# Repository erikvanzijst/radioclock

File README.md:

# Radio Controlled Clock

This project contains a custom designed wall clock that syncs to the DCF77
atomic time broadcast radio signal from Germany to ensure accuracy at all
times. There are no buttons to set the time manually.

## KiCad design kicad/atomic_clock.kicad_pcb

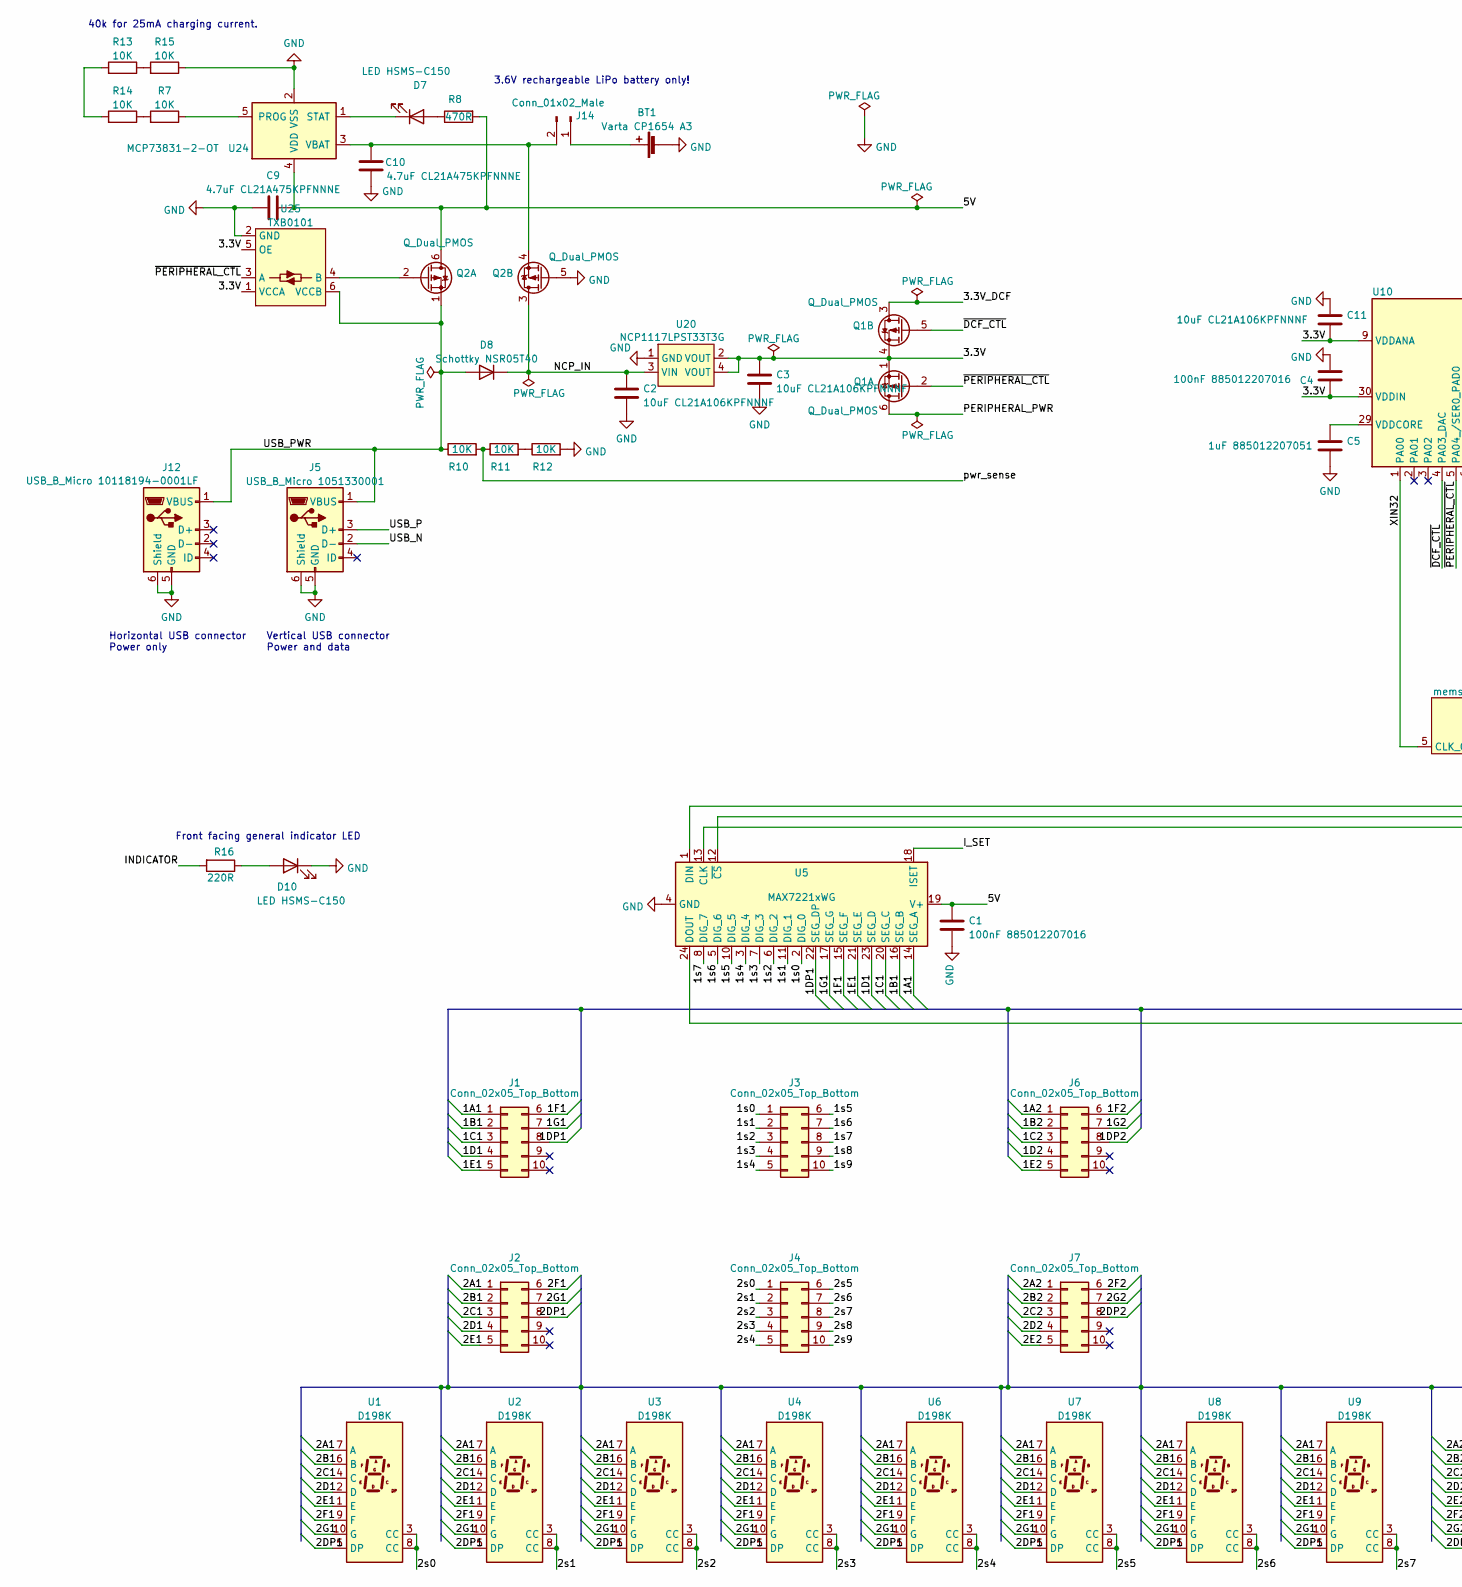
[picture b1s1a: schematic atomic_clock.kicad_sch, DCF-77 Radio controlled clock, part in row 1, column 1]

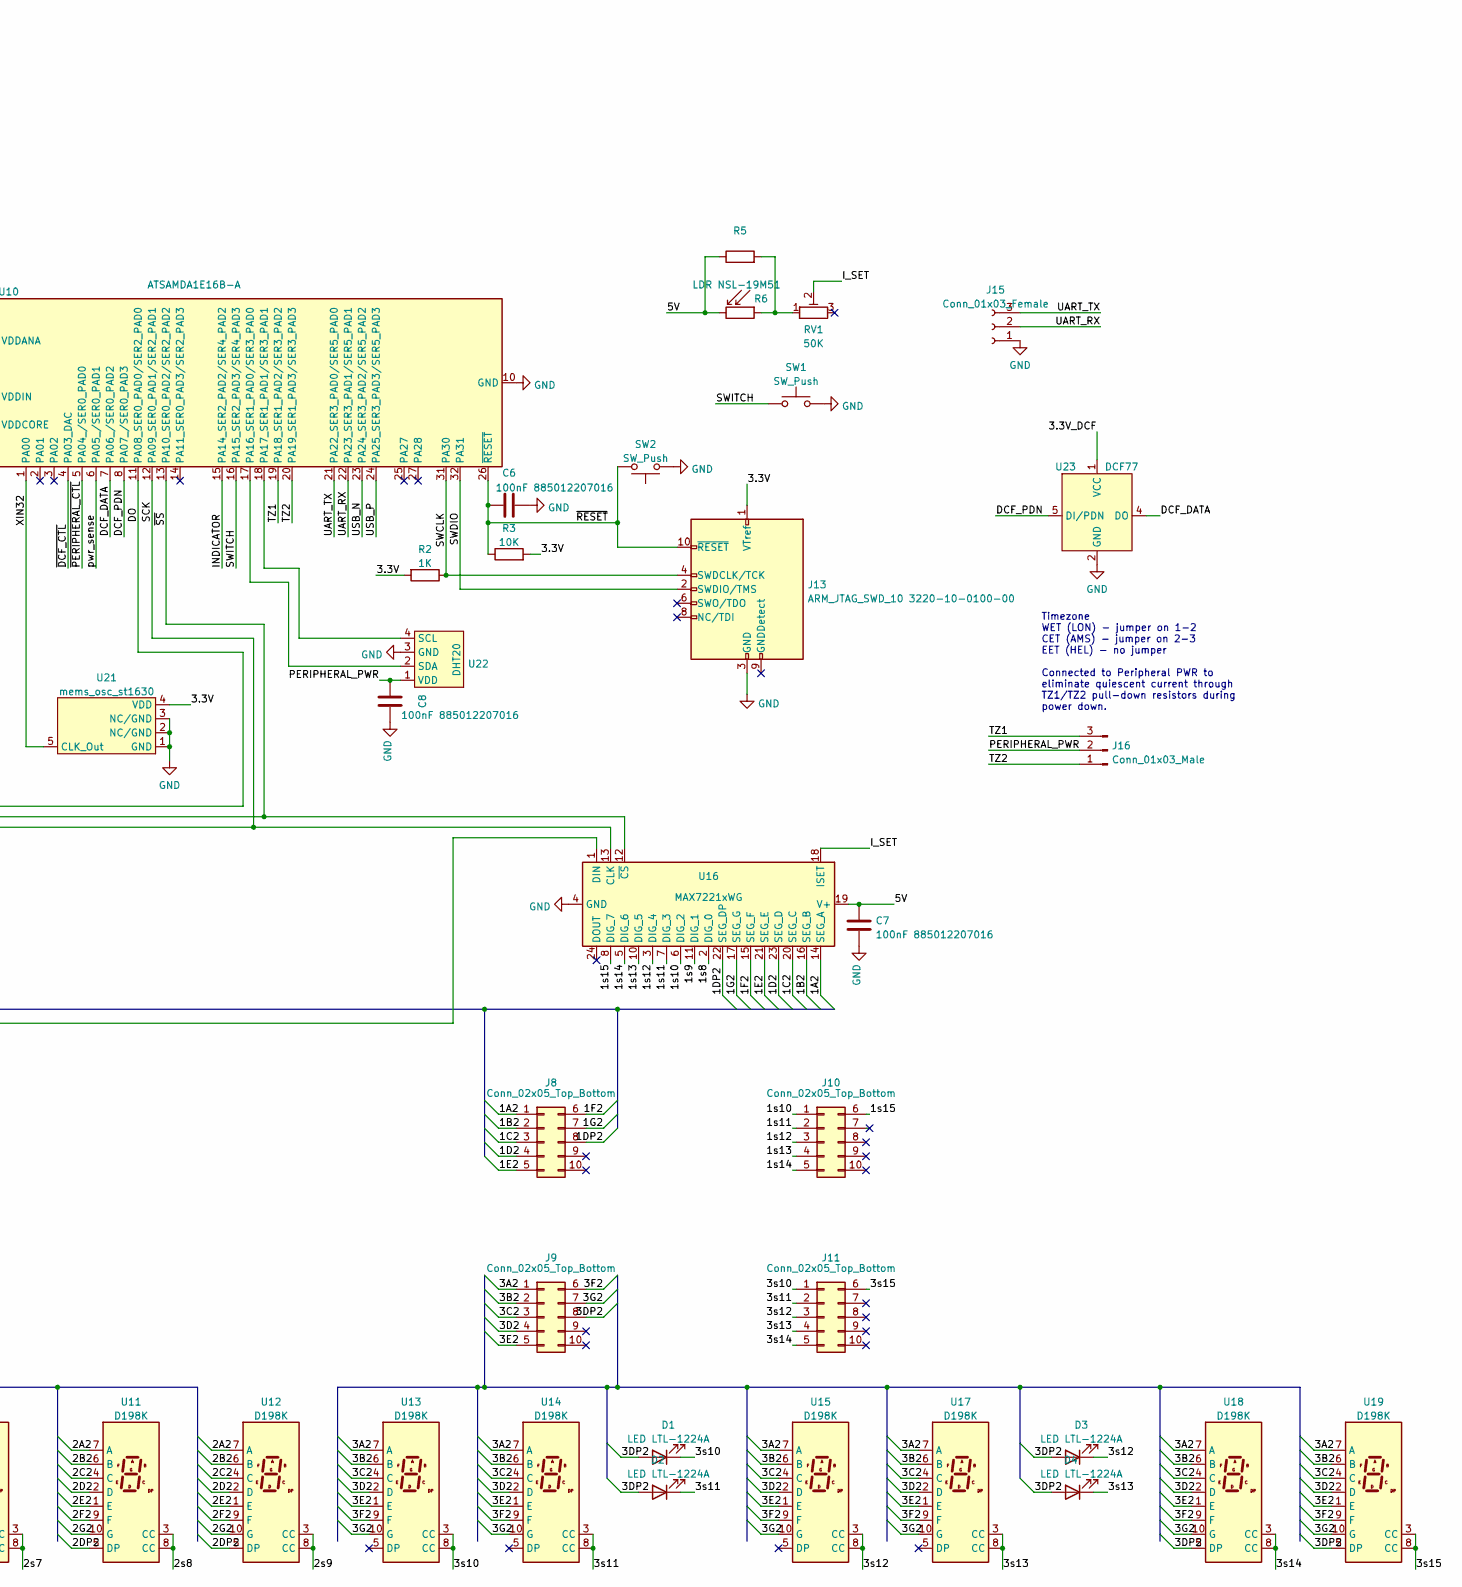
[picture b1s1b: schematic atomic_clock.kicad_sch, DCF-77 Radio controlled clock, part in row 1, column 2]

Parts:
BT1: Varta CP1654 A3; Battery_pads
C1, C4, C6, C7, C8: 100nF 885012207016; C_0805_2012Metric
C2, C3, C11: 10uF CL21A106KPFNNNF; C_0805_2012Metric
C5: 1uF 885012207051; C_0805_2012Metric
C9, C10: 4.7uF CL21A475KPFNNNE; C_0805_2012Metric
D1, D2, D3, D4: LED LTL-1224A; LED_D2.0mm_W4.8mm_H2.5mm_FlatTop
D7, D10: LED HSMS-C150; LED_1206_3216Metric_Pad1.42x1.75mm_HandSolder
D8: Schottky NSR05T40; D_SOD-523
J1, J2, J3, J4, J6, J7, J8, J9, J10, J11: Conn_02x05_Top_Bottom; PinHeader_2x05_P2.54mm_Vertical; DigiKey 67996-400HLF
J5: USB_B_Micro 1051330001; USB_Micro-B_Molex-105133-0001
J12: USB_B_Micro 10118194-0001LF; USB_Micro-B_Amphenol_10118194_Horizontal
J13: ARM_JTAG_SWD_10 3220-10-0100-00; sam_swd_header
J14: Conn_01x02_Male; PinHeader_1x02_P2.54mm_Vertical
J15: Conn_01x03_Female; PinSocket_1x03_P2.54mm_Vertical
J16: Conn_01x03_Male; PinHeader_1x03_P2.54mm_Vertical
Q1, Q2: Q_Dual_PMOS; SOT-363_SC-70-6
R2: 1K; R_0805_2012Metric
R3, R7, R10, R11, R12, R13, R14, R15: 10K; R_0805_2012Metric
R5: R_0805_2012Metric
R6: LDR NSL-19M51; R_LDR_4.9x4.2mm_P2.54mm_Vertical
R8: 470R; R_0805_2012Metric
R16: 220R; R_0805_2012Metric
RV1: 50K; Potentiometer_Bourns_TC33X_Vertical
SW1, SW2: SW_Push; SW_SPST_TL3342
U1, U2, U3, U4, U6, U7, U8, U9, U11, U12, U13, U14, U15, U17, U18, U19: D198K; D1X8K
U5, U16: MAX7221xWG; SOIC-24W_7.5x15.4mm_P1.27mm
U10: ATSAMDA1E16B-A; TQFP-32_7x7mm_P0.8mm
U20: NCP1117LPST33T3G; SOT-223
U21: mems_osc_st1630; SOT-23-5
U22: DHT20
U23: DCF77; DCF77 receiver module
U24: MCP73831-2-OT; SOT-23-5
U25: TXB0101; SOT-363_SC-70-6

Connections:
/1A1: J1.1, U5.14 (SEG_A)
/1A2: J6.1, J8.1, U16.14 (SEG_A)
/1B1: J1.2, U5.16 (SEG_B)
/1B2: J6.2, J8.2, U16.16 (SEG_B)
/1C1: J1.3, U5.20 (SEG_C)
/1C2: J6.3, J8.3, U16.20 (SEG_C)
/1D1: J1.4, U5.23 (SEG_D)
/1D2: J6.4, J8.4, U16.23 (SEG_D)
/1DP1: J1.8, U5.22 (SEG_DP)
/1DP2: J6.8, J8.8, U16.22 (SEG_DP)
/1E1: J1.5, U5.21 (SEG_E)
/1E2: J6.5, J8.5, U16.21 (SEG_E)
/1F1: J1.6, U5.15 (SEG_F)
/1F2: J6.6, J8.6, U16.15 (SEG_F)
/1G1: J1.7, U5.17 (SEG_G)
/1G2: J6.7, J8.7, U16.17 (SEG_G)
/1s0: J3.1, U5.2 (DIG_0)
/1s1: J3.2, U5.11 (DIG_1)
/1s2: J3.3, U5.6 (DIG_2)
/1s3: J3.4, U5.7 (DIG_3)
/1s4: J3.5, U5.3 (DIG_4)
/1s5: J3.6, U5.10 (DIG_5)
/1s6: J3.7, U5.5 (DIG_6)
/1s7: J3.8, U5.8 (DIG_7)
/1s8: J3.9, U16.2 (DIG_0)
/1s9: J3.10, U16.11 (DIG_1)
/1s10: J10.1, U16.6 (DIG_2)
/1s11: J10.2, U16.7 (DIG_3)
/1s12: J10.3, U16.3 (DIG_4)
/1s13: J10.4, U16.10 (DIG_5)
/1s14: J10.5, U16.5 (DIG_6)
/1s15: J10.6, U16.8 (DIG_7)
/2A1: J2.1, U1.7 (A), U2.7 (A), U3.7 (A), U4.7 (A), U6.7 (A), U7.7 (A), U8.7 (A), U9.7 (A)
/2A2: J7.1, U11.7 (A), U12.7 (A)
/2B1: J2.2, U1.6 (B), U2.6 (B), U3.6 (B), U4.6 (B), U6.6 (B), U7.6 (B), U8.6 (B), U9.6 (B)
/2B2: J7.2, U11.6 (B), U12.6 (B)
/2C1: J2.3, U1.4 (C), U2.4 (C), U3.4 (C), U4.4 (C), U6.4 (C), U7.4 (C), U8.4 (C), U9.4 (C)
/2C2: J7.3, U11.4 (C), U12.4 (C)
/2D1: J2.4, U1.2 (D), U2.2 (D), U3.2 (D), U4.2 (D), U6.2 (D), U7.2 (D), U8.2 (D), U9.2 (D)
/2D2: J7.4, U11.2 (D), U12.2 (D)
/2DP1: J2.8, U1.5 (DP), U2.5 (DP), U3.5 (DP), U4.5 (DP), U6.5 (DP), U7.5 (DP), U8.5 (DP), U9.5 (DP)
/2DP2: J7.8, U11.5 (DP), U12.5 (DP)
/2E1: J2.5, U1.1 (E), U2.1 (E), U3.1 (E), U4.1 (E), U6.1 (E), U7.1 (E), U8.1 (E), U9.1 (E)
/2E2: J7.5, U11.1 (E), U12.1 (E)
/2F1: J2.6, U1.9 (F), U2.9 (F), U3.9 (F), U4.9 (F), U6.9 (F), U7.9 (F), U8.9 (F), U9.9 (F)
/2F2: J7.6, U11.9 (F), U12.9 (F)
/2G1: J2.7, U1.10 (G), U2.10 (G), U3.10 (G), U4.10 (G), U6.10 (G), U7.10 (G), U8.10 (G), U9.10 (G)
/2G2: J7.7, U11.10 (G), U12.10 (G)
/2s0: J4.1, U1.3 (CC), U1.8 (CC)
/2s1: J4.2, U2.3 (CC), U2.8 (CC)
/2s2: J4.3, U3.3 (CC), U3.8 (CC)
/2s3: J4.4, U4.3 (CC), U4.8 (CC)
/2s4: J4.5, U6.3 (CC), U6.8 (CC)
/2s5: J4.6, U7.3 (CC), U7.8 (CC)
/2s6: J4.7, U8.3 (CC), U8.8 (CC)
/2s7: J4.8, U9.3 (CC), U9.8 (CC)
/2s8: J4.9, U11.3 (CC), U11.8 (CC)
/2s9: J4.10, U12.3 (CC), U12.8 (CC)
/3.3V: C3.1, C4.1, C11.1, J13.1 (VTref), Q1.1 (S), Q1.4 (S), R2.2, R3.2, U10.9 (VDDANA), U10.30 (VDDIN), U20.2 (VOUT), U20.4 (VOUT), U21.4 (VDD), U25.1 (VCCA), U25.5 (OE)
/3.3V_DCF: Q1.3 (D), U23.1 (VCC)
/3A2: J9.1, U13.7 (A), U14.7 (A), U15.7 (A), U17.7 (A), U18.7 (A), U19.7 (A)
/3B2: J9.2, U13.6 (B), U14.6 (B), U15.6 (B), U17.6 (B), U18.6 (B), U19.6 (B)
/3C2: J9.3, U13.4 (C), U14.4 (C), U15.4 (C), U17.4 (C), U18.4 (C), U19.4 (C)
/3D2: J9.4, U13.2 (D), U14.2 (D), U15.2 (D), U17.2 (D), U18.2 (D), U19.2 (D)
/3DP2: D1.2 (A), D2.2 (A), D3.2 (A), D4.2 (A), J9.8, U18.5 (DP), U19.5 (DP)
/3E2: J9.5, U13.1 (E), U14.1 (E), U15.1 (E), U17.1 (E), U18.1 (E), U19.1 (E)
/3F2: J9.6, U13.9 (F), U14.9 (F), U15.9 (F), U17.9 (F), U18.9 (F), U19.9 (F)
/3G2: J9.7, U13.10 (G), U14.10 (G), U15.10 (G), U17.10 (G), U18.10 (G), U19.10 (G)
/3s10: D1.1 (K), J11.1, U13.3 (CC), U13.8 (CC)
/3s11: D2.1 (K), J11.2, U14.3 (CC), U14.8 (CC)
/3s12: D3.1 (K), J11.3, U15.3 (CC), U15.8 (CC)
/3s13: D4.1 (K), J11.4, U17.3 (CC), U17.8 (CC)
/3s14: J11.5, U18.3 (CC), U18.8 (CC)
/3s15: J11.6, U19.3 (CC), U19.8 (CC)
/5V: C1.1, C7.1, C9.1, Q2.6 (D), R5.1, R6.2, R8.2, U5.19 (V+), U16.19 (V+), U24.4 (VDD)
/DCF_DATA: U10.7 (PA06_/SER0_PAD2), U23.4 (DO)
/DCF_PDN: U10.8 (PA07_/SER0_PAD3), U23.5 (DI/PDN)
/DO: U5.1 (DIN), U10.11 (PA08_SER0_PAD0/SER2_PAD0)
/INDICATOR: R16.2, U10.15 (PA14_SER2_PAD2/SER4_PAD2)
/I_SET: RV1.2, U5.18 (ISET), U16.18 (ISET)
/NCP_IN: C2.1, D8.1 (K), Q2.3 (D), U20.3 (VIN)
/PERIPHERAL_PWR: C8.1, J16.2, Q1.6 (D), U22.1 (VDD)
/SCK: U5.13 (CLK), U10.12 (PA09_SER0_PAD1/SER2_PAD1), U16.13 (CLK)
/SWCLK: J13.4 (SWDCLK/TCK), R2.1, U10.31 (PA30)
/SWDIO: J13.2 (SWDIO/TMS), U10.32 (PA31)
/SWITCH: SW1.1, U10.16 (PA15_SER2_PAD3/SER4_PAD3)
/TZ1: J16.3, U10.19 (PA18_SER1_PAD2/SER3_PAD2)
/TZ2: J16.1, U10.20 (PA19_SER1_PAD3/SER3_PAD3)
/UART_RX: J15.2, U10.22 (PA23_SER3_PAD1/SER5_PAD1)
/UART_TX: J15.3, U10.21 (PA22_SER3_PAD0/SER5_PAD0)
/USB_N: J5.2 (D-), U10.23 (PA24_SER3_PAD2/SER5_PAD2)
/USB_P: J5.3 (D+), U10.24 (PA25_SER3_PAD3/SER5_PAD3)
/USB_PWR: D8.2 (A), J5.1 (VBUS), J12.1 (VBUS), Q2.1 (S), R10.1, U25.6 (VCCB)
/XIN32: U10.1 (PA00), U21.5 (CLK_Out)
/pwr_sense: R10.2, R11.1, U10.6 (PA05_/SER0_PAD1)
/~DCF_CTL: Q1.5 (G), U10.4 (PA03_DAC)
/~PERIPHERAL_CTL: Q1.2 (G), U10.5 (PA04_/SER0_PAD0), U25.3 (A)
/~RESET: C6.1, J13.10 (~RESET), R3.1, SW2.2, U10.26 (~RESET)
/~SS: U5.12 (~CS), U10.13 (PA10_SER0_PAD2/SER2_PAD2), U16.12 (~CS)
GND: BT1.2 (-), C1.2, C2.2, C3.2, C4.2, C5.2, C6.2, C7.2, C8.2, C9.2, C10.1, C11.2, D10.1 (K), J5.5 (GND), J5.6 (Shield), J12.5 (GND), J12.6 (Shield), J13.3 (GND), J13.5 (GND), J15.1, Q2.5 (G), R12.2, R15.1, SW1.2, SW2.1, U5.4 (GND), U5.9 (GND), U10.10 (GND), U10.28 (GND), U16.4 (GND), U16.9 (GND), U20.1 (GND), U21.1 (GND), U21.2 (NC/GND), U21.3 (NC/GND), U22.3 (GND), U23.2 (GND), U24.2 (VSS), U25.2 (GND)
unnamed: BT1.1 (+), J14.1
unnamed: C5.1, U10.29 (VDDCORE)
unnamed: C10.2, J14.2, Q2.4 (S), U24.3 (VBAT)
unnamed: D7.1 (K), U24.1 (STAT)
unnamed: D7.2 (A), R8.1
unnamed: D10.2 (A), R16.1
unnamed: Q2.2 (G), U25.4 (B)
unnamed: R5.2, R6.1, RV1.1
unnamed: R7.1, U24.5 (PROG)
unnamed: R11.2, R12.1
unnamed: R13.1, R15.2
unnamed: R13.2, R14.2
unnamed: R7.2, R14.1
unnamed: U10.17 (PA16_SER1_PAD0/SER3_PAD0), U22.2 (SDA)
unnamed: U10.18 (PA17_SER1_PAD1/SER3_PAD1), U22.4 (SCL)
unnamed: U5.24 (DOUT), U16.1 (DIN)

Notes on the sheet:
40k for 25mA charging current.
Front facing general indicator LED
Vertical USB connector Power and data
3.6V rechargeable LiPo battery only!
Timezone WET (LON) - jumper on 1-2 CET (AMS) - jumper on 2-3 EET (HEL) - no jumper Connected to Peripheral PWR to eliminate quiescent current through TZ1/TZ2 pull-down resistors during power down.
Horizontal USB connector Power only

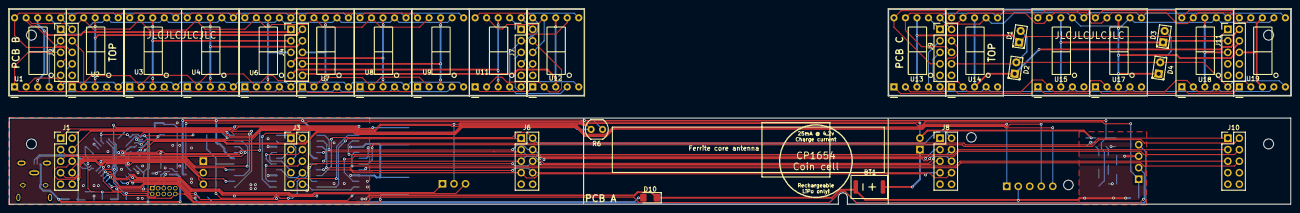
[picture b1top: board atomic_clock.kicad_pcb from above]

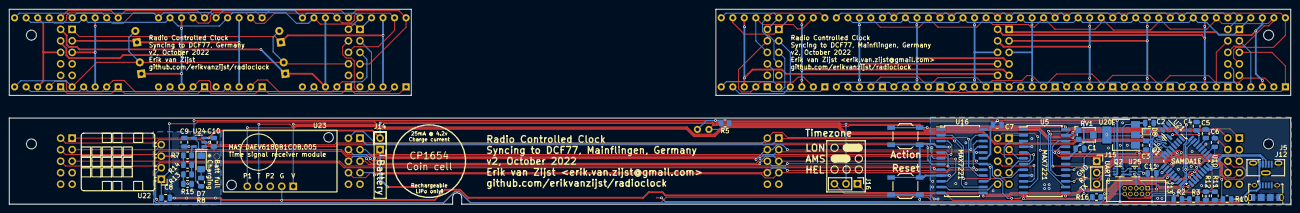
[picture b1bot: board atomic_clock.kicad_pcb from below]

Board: 2 copper layers, 282.7 x 43.0 mm, 78 parts (45 on the bottom side), 116 nets.

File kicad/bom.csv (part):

"Source:","/Users/erik/work/atomic_clock/kicad/atomic_clock.kicad_sch"
"Date:","Monday, June 06, 2022 at 12:07:27 AM"
"Tool:","Eeschema (6.0.4-0)"
"Generator:","/Applications/KiCad/KiCad.app/Contents/SharedSupport/plugins/bom_csv_grouped_by_value.py"
"Component Count:","80"

"Individual Components:"

"Item","Qty","Reference(s)","Value","LibPart","Footprint","Datasheet","Mfr","Mfr No.","Notes"
"","","BT1","Varta CP1654 A3","Device:Battery_Cell","local_footprints:Battery_pads","https://www.texim-europe.com/product/63165201018-VAR","","",""
"","","C1","100nF 885012207016","Device:C","Capacitor_SMD:C_0805_2012Metric","https://www.mouser.be/datasheet/2/445/885012207016-1727611.pdf","","",""
"","","C2","10uF CL21A106KPFNNNF","Device:C","Capacitor_SMD:C_0805_2012Metric","https://www.mouser.be/datasheet/2/585/MLCC-1837944.pdf","","",""
"","","C3","10uF CL21A106KPFNNNF","Device:C","Capacitor_SMD:C_0805_2012Metric","https://www.mouser.be/datasheet/2/585/MLCC-1837944.pdf","","",""
"","","C4","100nF 885012207016","Device:C","Capacitor_SMD:C_0805_2012Metric","https://www.mouser.be/datasheet/2/445/885012207016-1727611.pdf","","",""
"","","C5","1uF 885012207051","Device:C","Capacitor_SMD:C_0805_2012Metric","https://www.mouser.be/datasheet/2/445/885012207051-1727669.pdf","","",""
"","","C6","100nF 885012207016","Device:C","Capacitor_SMD:C_0805_2012Metric","https://www.mouser.be/datasheet/2/445/885012207016-1727611.pdf","","",""
"","","C7","100nF 885012207016","Device:C","Capacitor_SMD:C_0805_2012Metric","https://www.mouser.be/datasheet/2/445/885012207016-1727611.pdf","","",""
"","","C8","100nF 885012207016","Device:C","Capacitor_SMD:C_0805_2012Metric","https://www.mouser.be/datasheet/2/445/885012207016-1727611.pdf","","",""
"","","C9","4.7uF CL21A475KPFNNNE","Device:C","Capacitor_SMD:C_0805_2012Metric","https://www.mouser.be/datasheet/2/585/MLCC-1837944.pdf","","",""
"","","C10","4.7uF CL21A475KPFNNNE","Device:C","Capacitor_SMD:C_0805_2012Metric","https://www.mouser.be/datasheet/2/585/MLCC-1837944.pdf","","",""
"","","C11","10uF CL21A106KPFNNNF","Device:C","Capacitor_SMD:C_0805_2012Metric","https://www.mouser.be/datasheet/2/585/MLCC-1837944.pdf","","",""
"","","D1","LED LTL-1224A","Device:LED","local_footprints:LED_D2.0mm_W4.8mm_H2.5mm_FlatTop","https://www.mouser.be/datasheet/2/239/lite-on_lites03148-1-1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","","",""
"","","D2","LED LTL-1224A","Device:LED","local_footprints:LED_D2.0mm_W4.8mm_H2.5mm_FlatTop","https://www.mouser.be/datasheet/2/239/lite-on_lites03148-1-1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","","",""
"","","D3","LED LTL-1224A","Device:LED","local_footprints:LED_D2.0mm_W4.8mm_H2.5mm_FlatTop","https://www.mouser.be/datasheet/2/239/lite-on_lites03148-1-1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","","",""
"","","D4","LED LTL-1224A","Device:LED","local_footprints:LED_D2.0mm_W4.8mm_H2.5mm_FlatTop","https://www.mouser.be/datasheet/2/239/lite-on_lites03148-1-1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","","",""
"","","D5","Diode S1M-13-F","Device:D","Diode_SMD:D_SMA","https://www.mouser.be/datasheet/2/115/DIOD_S_A0007810797_1-2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","","",""
"","","D6","Diode S1M-13-F","Device:D","Diode_SMD:D_SMA","https://www.mouser.be/datasheet/2/115/DIOD_S_A0007810797_1-2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","","",""
"","","D7","LED HSMS-C150","Device:LED","LED_SMD:LED_1206_3216Metric_Pad1.42x1.75mm_HandSolder","https://www.mouser.be/datasheet/2/678/av02-0551en-ds-hsmx-cx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","","",""
"","","D8","Diode S1M-13-F","Device:D","Diode_SMD:D_SMA","https://www.mouser.be/datasheet/2/115/DIOD_S_A0007810797_1-2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","","",""
"","","D9","Diode S1M-13-F","Device:D","Diode_SMD:D_SMA","https://www.mouser.be/datasheet/2/115/DIOD_S_A0007810797_1-2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","","",""
"","","D10","LED HSMS-C150","Device:LED","LED_SMD:LED_1206_3216Metric_Pad1.42x1.75mm_HandSolder","https://www.mouser.be/datasheet/2/678/av02-0551en-ds-hsmx-cx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","","",""
"","","J1","Conn_02x05_Top_Bottom","Connector_Generic:Conn_02x05_Top_Bottom","Connector_PinHeader_2.54mm:PinHeader_2x05_P2.54mm_Vertical","~","","",""
"","","J2","Conn_02x05_Top_Bottom","Connector_Generic:Conn_02x05_Top_Bottom","Connector_PinHeader_2.54mm:PinHeader_2x05_P2.54mm_Vertical","~","","",""
"","","J3","Conn_02x05_Top_Bottom","Connector_Generic:Conn_02x05_Top_Bottom","Connector_PinHeader_2.54mm:PinHeader_2x05_P2.54mm_Vertical","~","","",""
"","","J4","Conn_02x05_Top_Bottom","Connector_Generic:Conn_02x05_Top_Bottom","Connector_PinHeader_2.54mm:PinHeader_2x05_P2.54mm_Vertical","~","","",""
"","","J5","USB_B_Micro 1051330001","Connector:USB_B_Micro","Connector_USB:USB_Micro-B_Molex-105133-0001","https://www.molex.com/pdm_docs/sd/1051330001_sd.pdf","","",""
"","","J6","Conn_02x05_Top_Bottom","Connector_Generic:Conn_02x05_Top_Bottom","Connector_PinHeader_2.54mm:PinHeader_2x05_P2.54mm_Vertical","~","","",""
"","","J7","Conn_02x05_Top_Bottom","Connector_Generic:Conn_02x05_Top_Bottom","Connector_PinHeader_2.54mm:PinHeader_2x05_P2.54mm_Vertical","~","","",""
"","","J8","Conn_02x05_Top_Bottom","Connector_Generic:Conn_02x05_Top_Bottom","Connector_PinHeader_2.54mm:PinHeader_2x05_P2.54mm_Vertical","~","","",""
"","","J9","Conn_02x05_Top_Bottom","Connector_Generic:Conn_02x05_Top_Bottom","Connector_PinHeader_2.54mm:PinHeader_2x05_P2.54mm_Vertical","~","","",""
"","","J10","Conn_02x05_Top_Bottom","Connector_Generic:Conn_02x05_Top_Bottom","Connector_PinHeader_2.54mm:PinHeader_2x05_P2.54mm_Vertical","~","","",""
"","","J11","Conn_02x05_Top_Bottom","Connector_Generic:Conn_02x05_Top_Bottom","Connector_PinHeader_2.54mm:PinHeader_2x05_P2.54mm_Vertical","~","","",""
"","","J12","USB_B_Micro 10118194-0001LF",":USB_B_Micro_1","Connector_USB:USB_Micro-B_Amphenol_10118194_Horizontal","https://www.amphenol-icc.com/media/wysiwyg/files/drawing/101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","","",""
"","","J13","ARM_JTAG_SWD_10 3220-10-0100-00","Connector:Conn_ARM_JTAG_SWD_10","local_footprints:sam_swd_header","http://www.cnctech.us/pdfs/3220-XX-0100-00_.pdf","","","http://infocenter.arm.com/help/topic/com.arm.doc.ddi0314h/DD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"
"","","J14","Conn_01x03_Female","Connector:Conn_01x03_Female","Connector_PinSocket_2.54mm:PinSocket_1x03_P2.54mm_Vertical","~","","",""
"","","Q1","Q_Dual_PMOS","Device:Q_Dual_PMOS_S1G1D2S2G2D1","Package_TO_SOT_SMD:SOT-363_SC-70-6","https://www.mouser.be/datasheet/2/427/si1965dh-1764856.pdf",""," SI1965DH-T1-BE3",""
"","","Q2","Q_Dual_PMOS","Device:Q_Dual_PMOS_S1G1D2S2G2D1","Package_TO_SOT_SMD:SOT-363_SC-70-6","https://www.mouser.be/datasheet/2/427/si1965dh-1764856.pdf",""," SI1965DH-T1-BE3 ",""
"","","R1","10K","Device:R","Resistor_SMD:R_0805_2012Metric","https://www.mouser.be/datasheet/2/219/RK73H-1825326.pdf","","",""
"","","R2","1K","Device:R","Resistor_SMD:R_0805_2012Metric","https://www.mouser.be/datasheet/2/447/Yageo_03_18_2021_PYu_R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","RC0805FR-101KL","",""
"","","R3","10K","Device:R","Resistor_SMD:R_0805_2012Metric","https://www.mouser.be/datasheet/2/219/RK73H-1825326.pdf","","",""
"","","R4","10K","Device:R","Resistor_SMD:R_0805_2012Metric","https://www.mouser.be/datasheet/2/219/RK73H-1825326.pdf","","",""
"","","R5","10K","Device:R","Resistor_SMD:R_0805_2012Metric","https://www.mouser.be/datasheet/2/219/RK73H-1825326.pdf","","",""
"","","R6","LDR NSL-19M51","Device:R_Photo","OptoDevice:R_LDR_4.9x4.2mm_P2.54mm_Vertical","https://media.digikey.com/pdf/Data%20Sheets/Photonic%20Detet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","","",""
"","","R7","10K","Device:R","Resistor_SMD:R_0805_2012Metric","https://www.mouser.be/datasheet/2/219/RK73H-1825326.pdf","","",""
"","","R8","470R","Device:R","Resistor_SMD:R_0805_2012Metric","https://www.mouser.be/datasheet/2/219/RK73H-1825326.pdf","RK73H2ATTD4700F","",""
"","","R9","10K","Device:R","Resistor_SMD:R_0805_2012Metric","https://www.mouser.be/datasheet/2/219/RK73H-1825326.pdf","","",""
"","","R10","10K","Device:R","Resistor_SMD:R_0805_2012Metric","https://www.mouser.be/datasheet/2/219/RK73H-1825326.pdf","","",""
"","","R11","10K","Device:R","Resistor_SMD:R_0805_2012Metric","https://www.mouser.be/datasheet/2/219/RK73H-1825326.pdf","","",""
"","","R12","10K","Device:R","Resistor_SMD:R_0805_2012Metric","https://www.mouser.be/datasheet/2/219/RK73H-1825326.pdf","","",""
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
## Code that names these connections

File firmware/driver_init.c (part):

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#endif

	// Set pin direction to input
	gpio_set_pin_direction(PWR_SENSE, GPIO_DIRECTION_IN);

	gpio_set_pin_pull_mode(PWR_SENSE,
	                       // <y> Pull configuration
	                       // <id> pad_pull_config
	                       // <GPIO_PULL_OFF"> Off
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	                       // <GPIO_PULL_DOWN"> Pull-down
	                       GPIO_PULL_OFF);

	gpio_set_pin_function(PWR_SENSE, PINMUX_PA05A_EIC_EXTINT5);

	// Set pin direction to input
	gpio_set_pin_direction(DCF_DATA, GPIO_DIRECTION_IN);

	gpio_set_pin_pull_mode(DCF_DATA,
	                       // <y> Pull configuration
	                       // <id> pad_pull_config
	                       // <GPIO_PULL_OFF"> Off
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	                       // <GPIO_PULL_DOWN"> Pull-down
	                       GPIO_PULL_OFF);

	gpio_set_pin_function(DCF_DATA, PINMUX_PA06A_EIC_EXTINT6);

	// Set pin direction to input
	gpio_set_pin_direction(SWITCH, GPIO_DIRECTION_IN);

	gpio_set_pin_pull_mode(SWITCH,
	                       // <y> Pull configuration
	                       // <id> pad_pull_config
	                       // <GPIO_PULL_OFF"> Off
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	                       // <GPIO_PULL_DOWN"> Pull-down
	                       GPIO_PULL_UP);

	gpio_set_pin_function(SWITCH, PINMUX_PA15A_EIC_EXTINT15);

	ext_irq_init();
}
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{
	init_mcu();

	// GPIO on PA00

	// Set pin direction to input
	gpio_set_pin_direction(XIN32, GPIO_DIRECTION_IN);

	gpio_set_pin_pull_mode(XIN32,
	                       // <y> Pull configuration
	                       // <id> pad_pull_config
	                       // <GPIO_PULL_OFF"> Off
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	                       // <GPIO_PULL_DOWN"> Pull-down
	                       GPIO_PULL_OFF);

	gpio_set_pin_function(XIN32, GPIO_PIN_FUNCTION_OFF);

	// GPIO on PA03

	gpio_set_pin_level(DCF_CTL,
	                   // <y> Initial level
	                   // <id> pad_initial_level
	                   // <false"> Low
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	                   false);

	// Set pin direction to output
	gpio_set_pin_direction(DCF_CTL, GPIO_DIRECTION_OUT);

	gpio_set_pin_function(DCF_CTL, GPIO_PIN_FUNCTION_OFF);

	// GPIO on PA04

	gpio_set_pin_level(PERIPHERAL_CTL,
	                   // <y> Initial level
	                   // <id> pad_initial_level
	                   // <false"> Low
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	                   false);

	// Set pin direction to output
	gpio_set_pin_direction(PERIPHERAL_CTL, GPIO_DIRECTION_OUT);

	gpio_set_pin_function(PERIPHERAL_CTL, GPIO_PIN_FUNCTION_OFF);

	// GPIO on PA07

	gpio_set_pin_level(DCF_PDN,
	                   // <y> Initial level
	                   // <id> pad_initial_level
	                   // <false"> Low
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	                   false);

	// Set pin direction to output
	gpio_set_pin_direction(DCF_PDN, GPIO_DIRECTION_OUT);

	gpio_set_pin_function(DCF_PDN, GPIO_PIN_FUNCTION_OFF);

	// GPIO on PA10

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
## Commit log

2022-04-07 Initial commit with half a schematic and PCB
2022-04-07 Add MIT license
2022-04-09 Lay out part of PCB
2022-05-16 Progress on PCB
2022-05-18 Add datasheets
2022-05-19 Layout mostly done.
2022-05-19 Stretch PCB to accommodate the LDR.
2022-05-25 Add LIR1220 rechargable battery datasheet
2022-05-30 Add coin cell battery holder
2022-05-30 Add footprint for battery leads
2022-05-30 Reworked battery/power system
2022-06-01 Add new schematic symbols
2022-06-01 Finished PCB placement
2022-06-01 Start routing
2022-06-02 Routed PCB
2022-06-03 Added silkscreen commentary
2022-06-04 Switch Pfet from NTJD4152P to si1965dh due to availability
2022-06-04 Switched flat top LEDs
2022-06-04 Filled out datasheet and part numbers on almost all components
    So we can generate a BOM.
2022-06-04 Placed and routed decoupling cap on VDDANA
2022-06-05 Added general indicator LED
2022-06-05 Added BOM
2022-06-06 Add README
2022-06-06 Add image to README
2022-06-07 Getting ready for v1.0
2022-06-07 Version 1.0 for submission to JLCPCB
2022-06-08 Add appr prices to BOM
2022-06-13 More datasheets
2022-06-17 Add container unit for seconds indicators
    Laser-cut 2.5mm wooden parts, stacked to provide an enclosure for
    the seconds indicator LEDs.
2022-06-25 Add enclosure parts
2022-06-25 Finalized on seconds LEDs enclosure
    Now using 3d printed parts with 2.4mm LED diameter holes that come
    out well on KoLab's Ultimaker 3.
2022-06-27 Fix short circuit in LDO symbol and footprint
    The heatsink on the NCP1117LP LDO was incorrectly wired to GND, while
    this pin is actually connected to Vout, causing a short circuit on
    the assembled board.
    https://twitter.com/erikvanzijst/status/1541097400571420672
2022-06-27 Add SAMD datasheet
2022-06-28 Add stubs for firmware
    Bootstrapped with Atmel Start.
2022-06-28 Fix pull-up resistor on SWCLK
    See https://twitter.com/erikvanzijst/status/1541787726684585988
2022-06-28 Widen debug connector footprint
    The actual header is 12.70mm wide.
2022-06-28 Blinky working
2022-06-28 UART is working
2022-06-28 Add stdio to UART redirection
2022-06-29 Peripheral power line control verified.
2022-06-29 I2C communication with DHT20 sensor working
    Now printing the current temperature on the UART.
2022-06-29 Add I2C logic analyzer screenshot
2022-06-29 Add CRC8 checksum verification to I2C reads
2022-06-29 Add humidity to output
2022-06-29 Add firmware compile, flash and debug instructions
2022-06-29 Update firmware instructions
2022-06-29 Check I2C read return value
2022-06-29 Add template for laser-cut LED shrouds
2022-06-29 Add RTC and calendar
    Resulting firmware not running due to clock initialization issue.
2022-06-29 Firmware boots again, but the 32kHz calendar clock runs way to fast
2022-06-30 Add datasheet for the AHT20 chip
    This is the IC that is in the DHT20 module.
2022-06-30 Add DHT20 soft reset command at startup
    Also add Makefile target to start OpenOCD in daemon mode for CLion
    interactive debugging.
2022-06-30 Update debug instructions
2022-06-30 Add SPI driver
2022-06-30 Hook up displays
2022-06-30 Scroll the display as demo
2022-07-01 Enable drain for LDR
2022-07-01 Add ADC driver
    The curent configuration does not appear to be working properly yet.
2022-07-01 Stretch antenna holder by 1 mm
2022-07-01 Fix ADC in 8-bit mode
    This should match the range 0-255 fairly well onto bright light to
    almost total darkness.
2022-07-03 Hook up LDR ADC readings to display
    The display now automatically adjusts its brightness to ambient
    lighting conditions.
2022-07-22 Enable DCF data signal
2022-07-22 Use external interrupt on DCF_DATA pin
    So we don't need to poll the DCF_DATA line, but get notified when
    it toggles.
2022-07-22 Add interrupt handler for switch on PCB
2022-07-23 Add time decoder script
    Next is getting the microcontroller's clock system properly
    configured and then the decoder can be ported to it.
2022-07-23 Pulse LED at 1Hz while configuring system clocks
2022-07-23 Boost system clock from 8 to 24MHz
2022-07-23 Boost system clock from 24 to 48MHz
    48MHz requires NVM wait states or else the CPU halts.
2022-07-24 Add millis() wallclock function
    Implemented using a timer.
2022-07-24 Configure RTC/Calendar
2022-07-26 Add DCF decoding logic
    Also added a very low effort unit test implementation.
2022-07-27 Add rudimentary logging subsystem
    Logs go to UART and include timestamp, severity, filename, line number,
    function name, etc.
2022-07-27 Show calendar/rtc on display
    Keep the display powered off after boot to aid radio reception.
    Enable the display after the first successful radio capture.
2022-07-27 Collect misc functions in utils.c
2022-07-27 Make ADC conversions asynchronous to offload the CPU
2022-07-27 Enable external 32kHz MEMS oscillator for highly accurate RTC
2022-07-28 Use async IO for SPI
2022-07-28 Refactor DHT I2C code for asynchronous IO
2022-07-28 Switch to software 7-segment encoding
    So we can also display arbitrary symbols.
2022-07-28 Alternate display between date and temp/humidity
2022-07-30 Implement nightly syncs at 2am and 4am
2022-07-31 Button always forces a re-sync now
    Also powering down the DCF module when the display is running.
    There's way too much electromagnetic interference from the the
    display circuitry to get any reception.
2022-07-31 Add barebones USB serial logger script
2022-08-01 Fix ADC/LDR measurements and display brightness mapping
2022-08-01 Remove USB serial code from dcf.py
    Instead, pipe the output from ftdi.py into dcf.py.
2022-08-01 Switch date format to DD-MM-YYYY
2022-08-05 Turn off OSCULP32K, make button and DCF line wakeup interrupts
    Also added a second timer that runs in standby and might serve
    as way to implement DCF synchronization with the microcontroller
    mostly in standby mode.
2022-08-07 Put microcontroller in STANDBY state during radio broadcast
2022-08-07 Add TODO list for PCB v1.1
2022-08-07 Eliminate buffering and string decoding in python tools
2022-08-08 Improve Python and bash portability
2022-08-08 Wire up USB power sense, reset button and hibernation
2022-08-09 Add TODO for next PCB revision
2022-08-09 Fix I2C reinitialization bug after STANDBY
2022-08-09 Ignore errors in the first 20 DCF bits, we're not using them
2022-08-10 Add missing files for power management
2022-10-16 Add bootloader doco
2022-10-26 Start routing v2
2022-10-27 Route almost all of v2 PCB
2022-10-28 Completed place and route of v2
2022-10-28 Add schematic pdf
2022-10-29 Perform daily sync just after 3am
    This so we will quickly pick up the DST change.
2022-10-31 PCB v2 as submitted to JLCPCB
2022-11-01 Fix nightly sync alarms
    The nightly alarms never got triggered. This because alarms get
    pinned to their absolute RTC timestamp at firmware startup. Since
    the RTC is at epoch at init, the alarms get scheduled for 1/1/1970
    but then after the initial sync the clock jumps by half a century,
    past the RTC_MODE0_COMP_COMP register value and so the alarms would
    never trigger.
2022-11-01 Add CI
    Run tests and build the firmware.
2022-11-01 Fix tests
2022-11-01 Fix Actions workflow file
2022-11-01 Fix Actions workflow
2022-11-01 Build and archive firmware binary
2022-11-03 Make microcontroller chip configurable
    As the next batch will use a SAMDA1E15B with 32k flash due to supply
    shortages.
2022-11-03 Switch to custom ARM build container
    We need a more recent version of git to appease GitHub Actions.
2022-11-04 Add linker script for 32k microcontroller
2022-11-04 Refactor logging macro
    Don't inline the logging format strings everywhere. Merely inline a call to
    a function that contains the format strings and logic.
    This helps bring the binary under 32kb, necessary to fit the SAMDA1E15B used
    on version 2 of the PCB.
2022-11-04 Create 3 different firmware binaries
    Define different firmware configurations for the 3 PCB/microcontroller
    permutations we now have.
2022-11-04 Omit ADC code in v2 binaries
    PCB version 2 does not use the ADC, so leave out the ASF boilerplate.
2022-11-04 Add timezone jumper code
2022-11-06 Extract DST flag from DCF signal
2022-11-11 First stab at acrylic glass enclosure
2022-11-13 Drew the enclosure in PCBNew
2022-11-13 Fix pull-up bug on floating switch input
    This was causing random resets as a long-press of the button triggers
    _reset_mcu()
2022-11-16 Add datasheet for 50k trimpot
2022-11-17 Create separate OpenOCD conf files for uc variants
2022-11-18 Add a VERBOSE log level for DCF decoding updates
    And make LOG_LEVEL configurable at compile time.
2022-11-18 Tie all display signals to GND during time sync
2022-11-18 Always time out after 5 minutes of unsuccessful syncing
2022-11-19 Tune analog brightness control circuitry
    Real world testing showed the 10K resistor on each driver chip to
    be unnecessary and the 10MOhm parallel to the LDR to be overkill.
2022-11-21 Don't write to the UART from interrupt routines
2022-11-21 Move the USB connectors further from the board edge

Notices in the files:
kicad/atomic_clock.kicad_sch:
License: MIT
parts and their libraries:
© Semiconductor Components Industries, LLC, 2014 January, 2020 − Rev. 5 1 Publication Order Number: NCP1117LP/D Voltage Regulators, 1.0 A Low-Dropout Positive, Fixed and Adjustable
